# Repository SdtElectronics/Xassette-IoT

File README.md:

# Xassette IoT

## Hardware Resources
* SoC: MediaTek MT7628 1xMIPS 24Kc@580Mhz
* RAM: 64MB DDR2
* ROM: 8M SPI flash EN25Q64
* WLAN: 802.11n, 2T2R, speed up to 300Mbps
* EPHY: 5×100M with 2 onboard RJ-45 ports
* USB: 1×USB2.0 HS
* Connectivity: 2×UART¹, 1×I2C, 1×I2S, 1×SPI², 1×SDIO³, 4×PWM

Note:
1. UART1 is used as debug serial at baud rate 57600 with default firmware
2. Shared with onboard NOR flash
3. Supports SDXC up to 2TB

## Flashing New Firmware
* See [Guide on Firmware](docs/fwGuide.md)

## Build New Firmware From Source
* See [Build From Scratch](docs/buildingGuide.md)

## Schematic

PDF format is available at [hw/anBreakout.pdf](hw/anBreakout.pdf)

Note: `IOxx` in the schematic as well as the silk numbers onboard correspond to the GPIO indices in the table below.

## Board Gerber
See [Releases](https://github.com/SdtElectronics/Xassette-IoT/releases/)

## Errata
In v0.2
* Silk text error: MDI1 should be MDI2
* Net error: 1V8 is not connected
* Annotation and silk text error: pin45 should be pin12
* Annotation and silk text error: pin46 should be pin13

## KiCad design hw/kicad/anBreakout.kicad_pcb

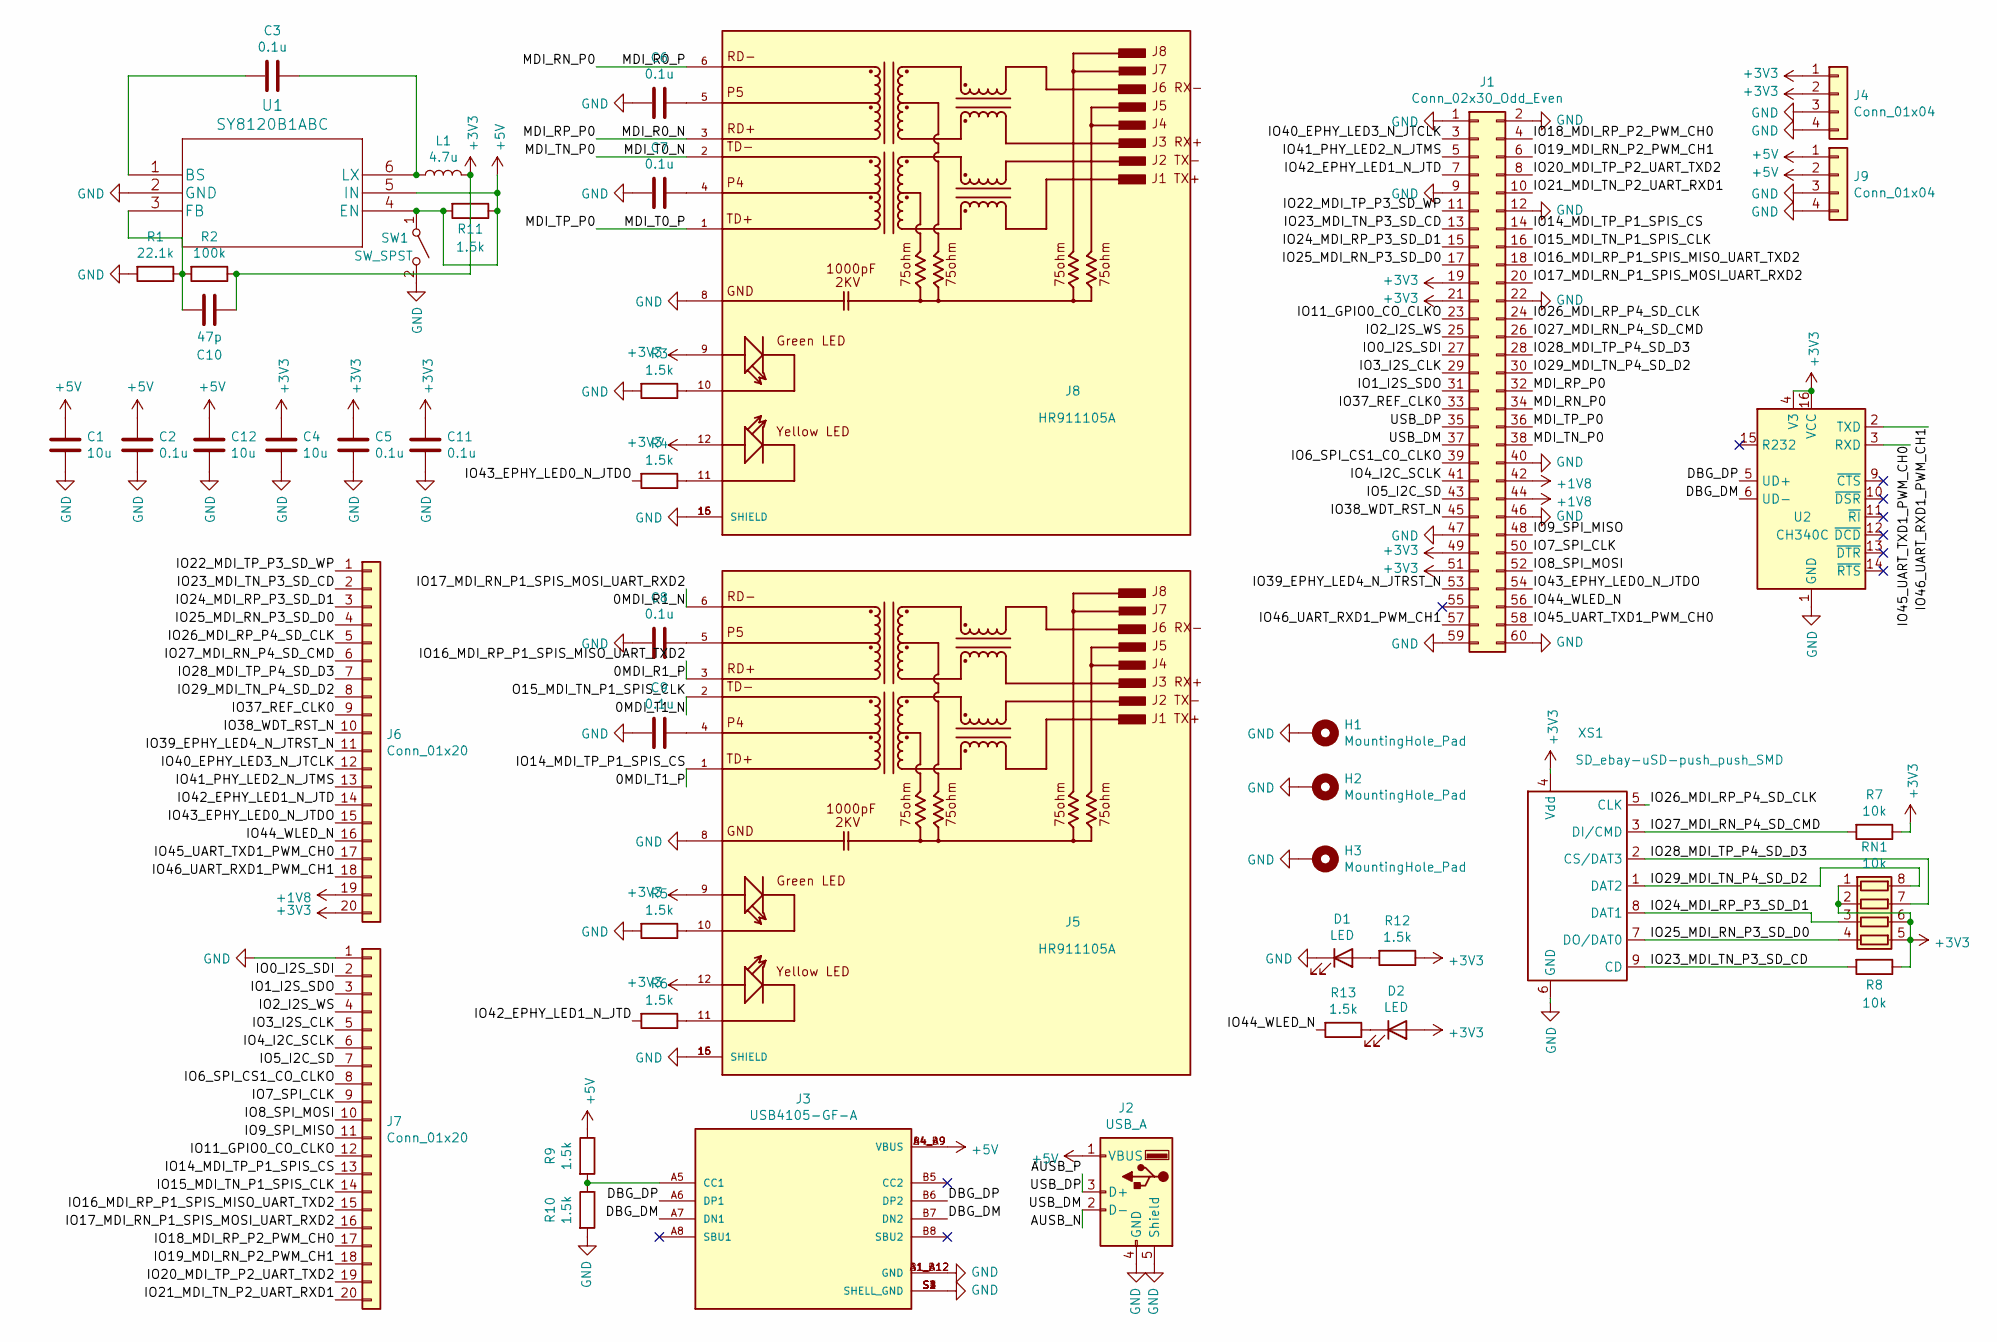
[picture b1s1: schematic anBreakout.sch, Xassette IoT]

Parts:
C1, C4, C12: 10u; C_0805_2012Metric
C2, C3, C5, C6, C7, C8, C9, C11: 0.1u; C_0603_1608Metric
C10: 47p; C_0603_1608Metric
D1, D2: LED; LED_0603_1608Metric
H1, H2, H3: MountingHole_Pad; MountingHole_3.2mm_M3_Pad
J1: Conn_02x30_Odd_Even; PinSocket_2x30_P1.27mm_Vertical_SMD
J2: USB_A; USB_A_Wuerth_614004134726_Horizontal
J3: USB4105-GF-A; GCT_USB4105-GF-A; PARTREV A3
J4, J9: Conn_01x04; PinHeader_1x04_P2.54mm_Horizontal
J5, J8: HR911105A; HANRUN_HR911105A; PARTREV A
J6, J7: Conn_01x20; PinHeader_1x20_P2.54mm_Vertical
L1: 4.7u; L_Taiyo-Yuden_MD-4040
R1: 22.1k; R_0603_1608Metric
R2: 100k; R_0603_1608Metric
R3, R4, R5, R6, R9, R10, R11, R12, R13: 1.5k; R_0603_1608Metric
R7, R8: 10k; R_0603_1608Metric
RN1: 10k; R_Array_Convex_4x0603
SW1: SW_SPST; SW_SPST_FSMSM
U1: SY8120B1ABC; SOT-23-6
U2: CH340C; SOIC-16_3.9x9.9mm_P1.27mm
XS1: SD_ebay-uSD-push_push_SMD; Conn_uSDcard

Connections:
+1V8: J1.42, J1.44, J6.19
+3V3: C4.2, C5.2, C10.1, C11.2, D2.2 (A), J1.19, J1.21, J1.49, J1.51, J4.1, J4.2, J5.9, J5.12, J6.20, J8.9, J8.12, L1.2, R2.1, R7.1, R8.1, R12.1, RN1.1 (R1.1), RN1.2 (R2.1), RN1.5 (R4.2), RN1.6 (R3.2), U2.4 (V3), U2.16 (VCC), XS1.4 (Vdd)
+5V: C1.2, C2.2, C12.2, J2.1 (VBUS), J3.A4_B9 (VBUS), J3.B4_A9 (VBUS), J9.1, J9.2, R9.1, R11.1, R11.2, SW1.1 (A), U1.4 (EN), U1.5 (IN)
/0MDI_R1_N: J1.20, J5.6, J7.16
/0MDI_R1_P: J1.18, J5.3, J7.15
/0MDI_T1_P: J1.14, J5.1, J7.13
/AUSB_N: J1.37, J2.2 (D-)
/AUSB_P: J1.35, J2.3 (D+)
/DBG_DM: J3.A7 (DN1), J3.B7 (DN2), U2.6 (UD-)
/DBG_DP: J3.A6 (DP1), J3.B6 (DP2), U2.5 (UD+)
/IO1_I2S_SDO: J1.31, J7.3
/IO2_I2S_WS: J1.25, J7.4
/IO3_I2S_CLK: J1.29, J7.5
/IO6_SPI_CS1_CO_CLKO: J1.39, J7.8
/IO7_SPI_CLK: J1.50, J7.9
/IO8_SPI_MOSI: J1.52, J7.10
/IO9_SPI_MISO: J1.48, J7.11
/IO11_GPIO0_CO_CLKO: J1.23, J7.12
/IO18_MDI_RP_P2_PWM_CH0: J1.4, J7.17
/IO19_MDI_RN_P2_PWM_CH1: J1.6, J7.18
/IO20_MDI_TP_P2_UART_TXD2: J1.8, J7.19
/IO21_MDI_TN_P2_UART_RXD1: J1.10, J7.20
/IO22_MDI_TP_P3_SD_WP: J1.11, J6.1
/IO23_MDI_TN_P3_SD_CD: J1.13, J6.2, R8.2, XS1.9 (CD)
/IO24_MDI_RP_P3_SD_D1: J1.15, J6.3, RN1.3 (R3.1), XS1.8 (DAT1)
/IO25_MDI_RN_P3_SD_D0: J1.17, J6.4, RN1.4 (R4.1), XS1.7 (DO/DAT0)
/IO26_MDI_RP_P4_SD_CLK: J1.24, J6.5, XS1.5 (CLK)
/IO27_MDI_RN_P4_SD_CMD: J1.26, J6.6, R7.2, XS1.3 (DI/CMD)
/IO28_MDI_TP_P4_SD_D3: J1.28, J6.7, RN1.7 (R2.2), XS1.2 (CS/DAT3)
/IO29_MDI_TN_P4_SD_D2: J1.30, J6.8, RN1.8 (R1.2), XS1.1 (DAT2)
/IO37_REF_CLK0: J1.33, J6.9
/IO39_EPHY_LED4_N_JTRST_N: J1.53, J6.11
/IO40_EPHY_LED3_N_JTCLK: J1.3, J6.12
/IO41_PHY_LED2_N_JTMS: J1.5, J6.13
/IO42_EPHY_LED1_N_JTD: J1.7, J6.14, R6.2
/IO43_EPHY_LED0_N_JTDO: J1.54, J6.15, R4.2
/IO44_WLED_N: J1.56, J6.16, R13.2
/IO45_UART_TXD1_PWM_CH0: J1.58, J6.17, U2.3 (RXD)
/IO46_UART_RXD1_PWM_CH1: J1.57, J6.18, U2.2 (TXD)
/MDI_R0_N: J1.32, J8.3
/MDI_R0_P: J1.34, J8.6
/MDI_T0_N: J1.38, J8.2
/MDI_T0_P: J1.36, J8.1
/O0_I2S_SDI: J1.27, J7.2
/O4_I2C_SCLK: J1.41, J7.6
/O5_I2C_SD: J1.43, J7.7
/O38_WDT_RST_N: J1.45, J6.10
GND: C1.1, C2.1, C4.1, C5.1, C6.2, C7.2, C8.2, C9.2, C11.1, C12.1, D1.1 (K), H1.1, H2.1, H3.1, J1.1, J1.2, J1.9, J1.12, J1.22, J1.40, J1.46, J1.47, J1.59, J1.60, J2.4 (GND), J2.5 (Shield), J3.A1_B12 (GND), J3.B1_A12 (GND), J3.S1 (SHELL_GND), J3.S2 (SHELL_GND), J3.S3 (SHELL_GND), J3.S4 (SHELL_GND), J4.3, J4.4, J5.8, J5.15 (SHIELD), J5.16 (SHIELD), J7.1, J8.8, J8.15 (SHIELD), J8.16 (SHIELD), J9.3, J9.4, R1.2, R3.2, R5.2, R10.2, SW1.2 (B), U1.2 (GND), U2.1 (GND), XS1.6 (GND)
unnamed: C3.1, L1.1, U1.6 (LX)
unnamed: C3.2, U1.1 (BS)
unnamed: C6.1, J8.5
unnamed: C7.1, J8.4
unnamed: C8.1, J5.5
unnamed: C9.1, J5.4
unnamed: C10.2, R1.1, R2.2, U1.3 (FB)
unnamed: D1.2 (A), R12.2
unnamed: D2.1 (K), R13.1
unnamed: J3.A5 (CC1), R9.2, R10.1
unnamed: J5.10, R5.1
unnamed: J5.11, R6.1
unnamed: J8.10, R3.1
unnamed: J8.11, R4.1

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
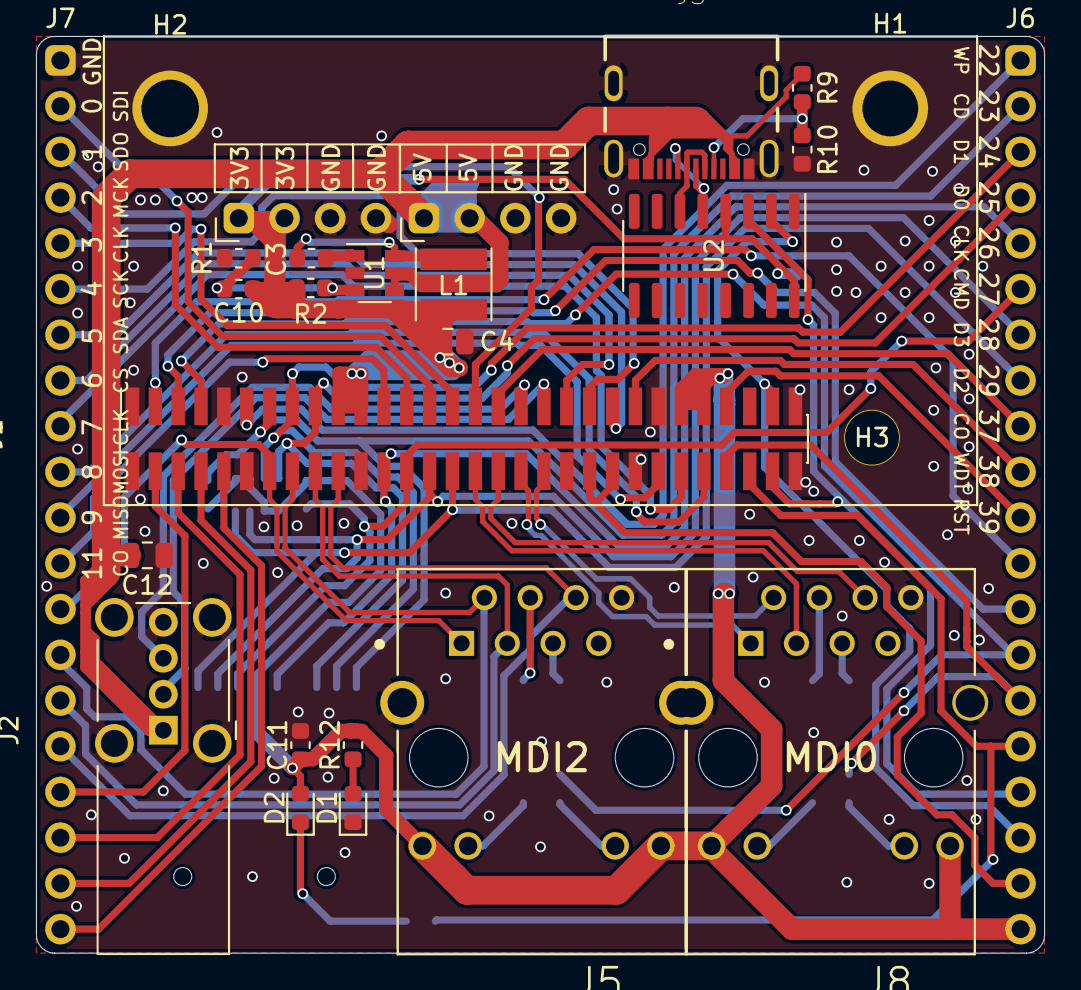
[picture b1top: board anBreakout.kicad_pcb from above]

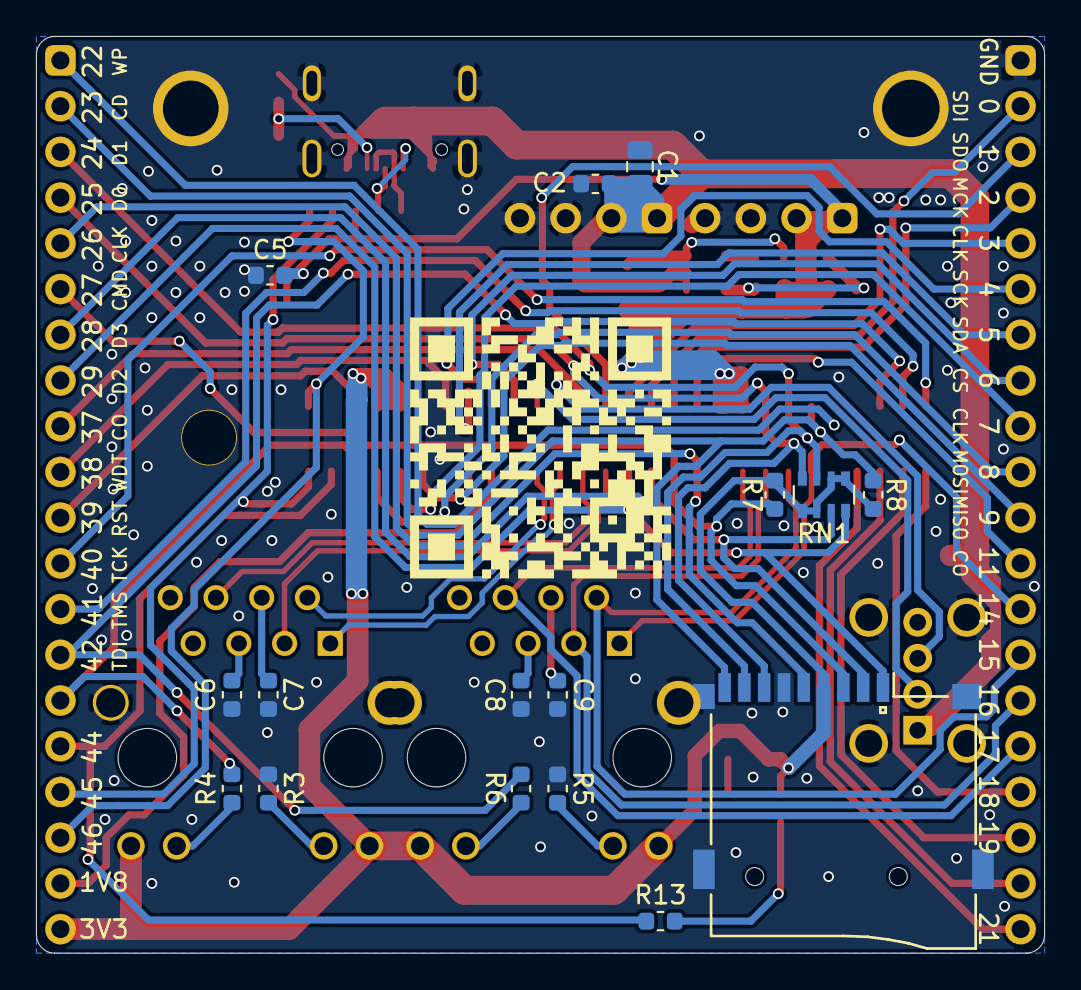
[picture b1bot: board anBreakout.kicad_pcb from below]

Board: 2 copper layers, 56.0 x 50.9 mm, 44 parts (17 on the bottom side), 63 nets.

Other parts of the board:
QR*****: https://github.com/SdtElectronics; __github.com_SdtElectronics

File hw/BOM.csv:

Comment,Designator,Footprint,Pins,Quantity
47p,"C10,",C_0603_1608Metric,2,1
0.1u,"C11,C3,",C_0603_1608Metric,2,2
10u,"C12,C4,",C_0805_2012Metric,2,2
LED,"D2,D1,",LED_0603_1608Metric,2,2
Conn_02x30_Odd_Even,"J1,",PinSocket_2x30_P1.27mm_Vertical_SMD,60,1
4.7u,"L1,",L_0420,2,1
22.1k,"R1,",R_0603_1608Metric,2,1
1.5k,"R12,R10,R9,",R_0603_1608Metric,2,3
100k,"R2,",R_0603_1608Metric,2,1
SY8120B1ABC,"U1,",SOT-23-6,6,1
CH340C,"U2,",SOIC-16_3.9x9.9mm_P1.27mm,16,1
10u,"C1,",C_0805_2012Metric,2,1
0.1u,"C9,C8,C7,C6,C5,C2,",C_0603_1608Metric,2,6
1.5k,"R13,R6,R5,R4,R3,",R_0603_1608Metric,2,5
10k,"R8,R7,",R_0603_1608Metric,2,2
10k,"RN1,",R_Array_Convex_4x0603,8,1
Through Hole Items,,,, 
USB_A,"J2,",USB_A_Wuerth_614004134726_Horizontal,8,1
USB4105-GF-A,"J3,",GCT_USB4105-GF-A,18,1
Conn_01x20,"J7,J6,",PinHeader_1x20_P2.54mm_Vertical,20,2
HR911105A,"J8,J5,",HANRUN_HR911105A,16,2
Conn_01x04,"J9,J4,",PinHeader_1x04_P2.54mm_Horizontal,4,2
uSD-push_push_SMD,"XS1,",Conn_uSDcard,15,1

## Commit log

2021-08-19 add documentations
2021-08-21 add BOM List
2021-08-21 update schematic
2021-08-24 add errata
2021-09-03 Add guide on building u-boot
2021-09-04 Add guide on building openwrt
2021-09-04 Add note about flash size
2021-09-30 amend uart pin index
2021-11-03 disclosure pcb sources
